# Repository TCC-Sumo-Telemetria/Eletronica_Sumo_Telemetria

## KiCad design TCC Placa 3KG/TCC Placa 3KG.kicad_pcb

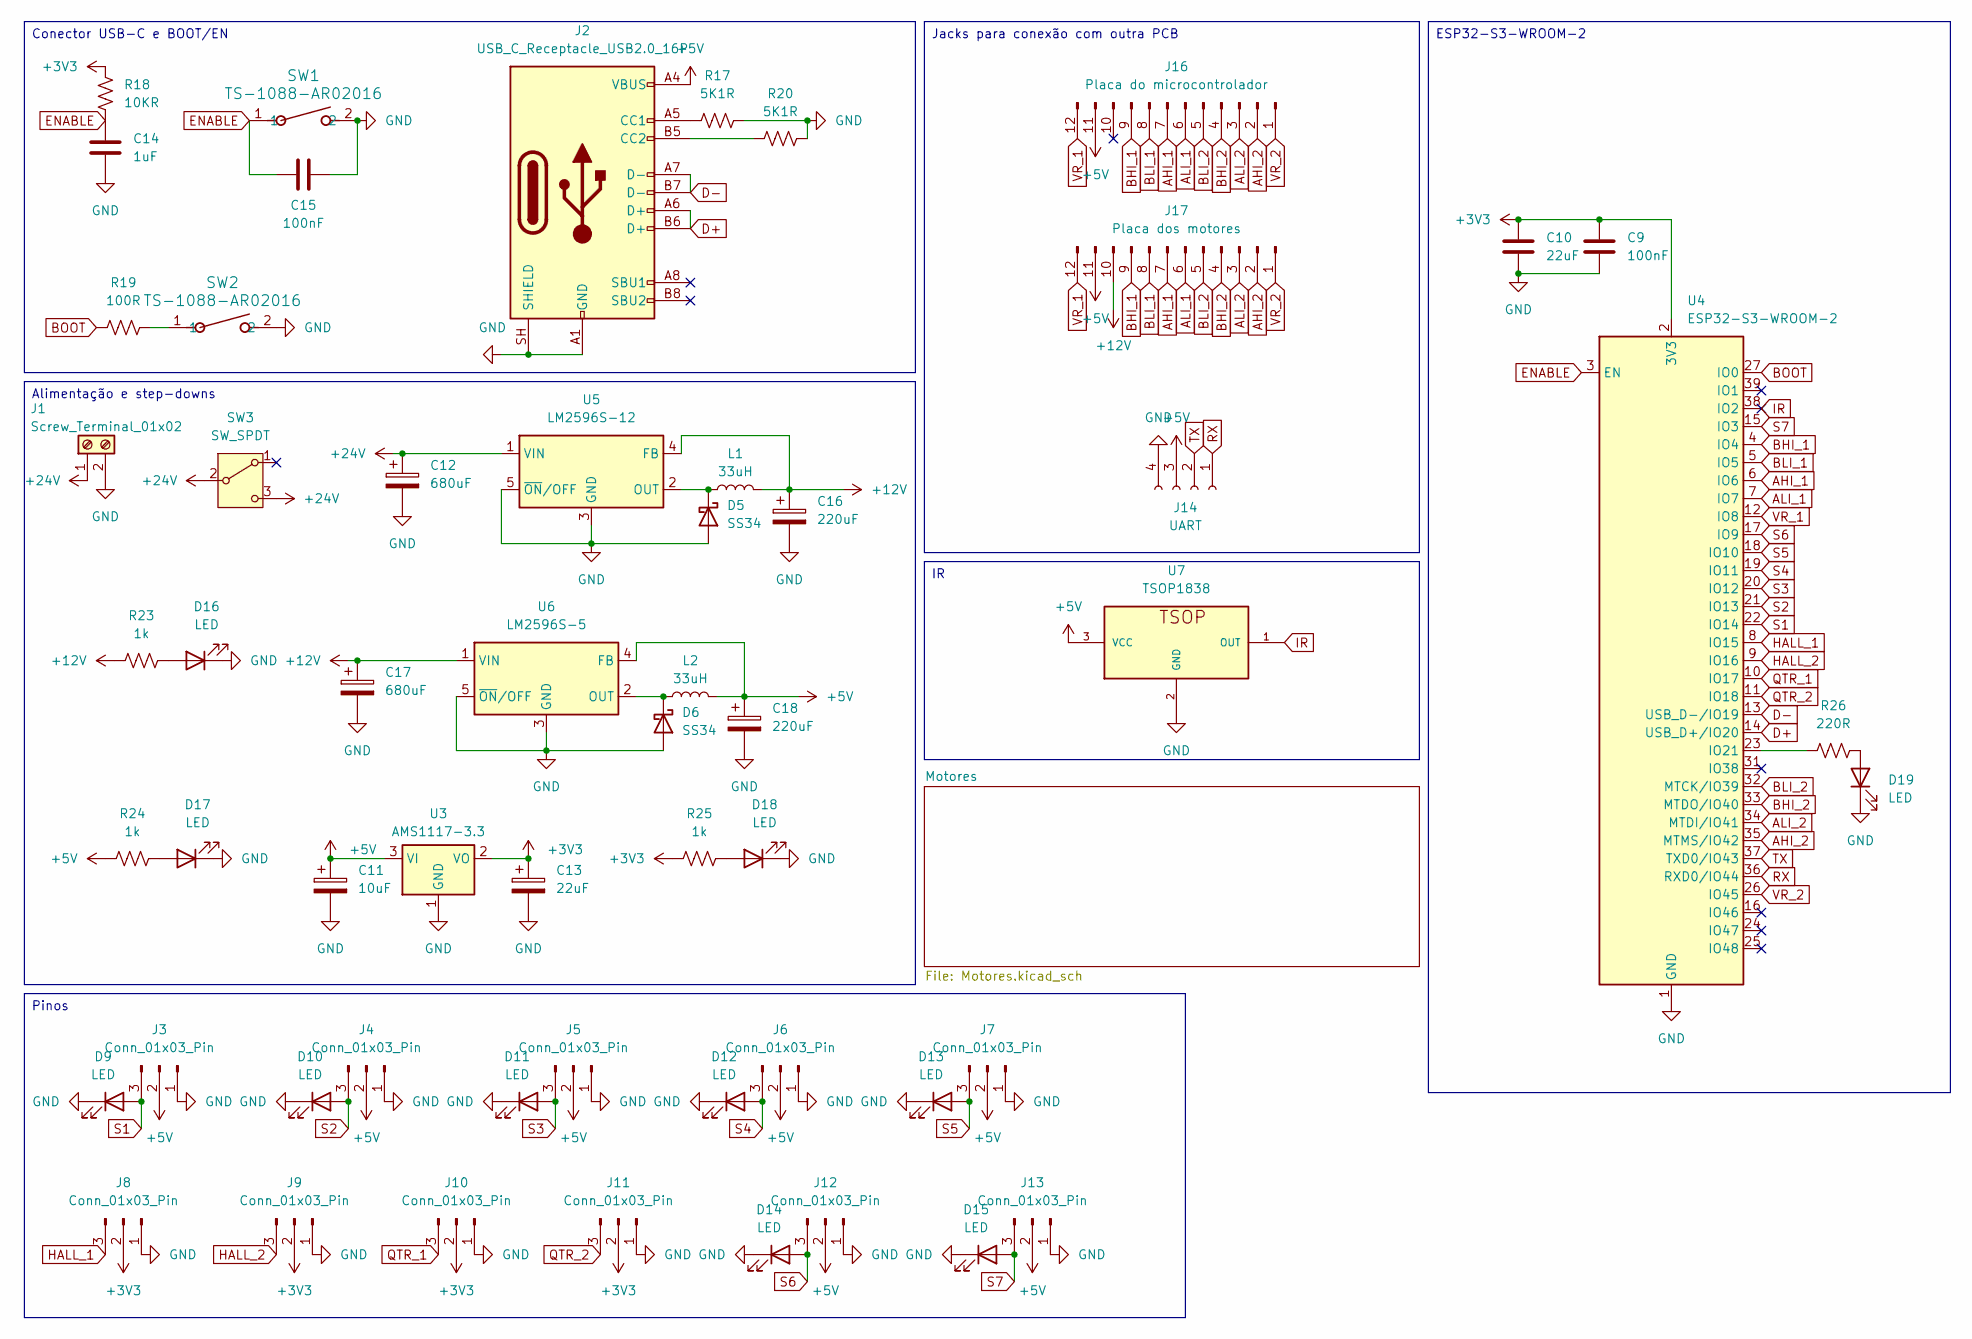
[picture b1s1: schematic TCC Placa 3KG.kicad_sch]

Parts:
C9: 100nF; C_0805_2012Metric
C10: 22uF; C_0805_2012Metric
C11: 10uF; CP_EIA-3528-21_Kemet-B_HandSolder
C12, C17: 680uF; CP_Radial_D10.0mm_P5.00mm
C13: 22uF; CP_EIA-3528-21_Kemet-B_HandSolder
C14: 1uF; C_0805_2012Metric_Pad1.18x1.45mm_HandSolder
C15: 100nF; C_0805_2012Metric_Pad1.18x1.45mm_HandSolder
C16, C18: 220uF; CP_Elec_8x10.5
D5, D6: SS34; D_SMA_Handsoldering
D9, D10, D11, D12, D13, D14, D15, D16, D17, D18, D19: LED; LED_0805_2012Metric_Pad1.15x1.40mm_HandSolder
J1: Screw_Terminal_01x02; TerminalBlock_MaiXu_MX126-5.0-02P_1x02_P5.00mm
J2: USB_C_Receptacle_USB2.0_16P; USB_C_Receptacle_G-Switch_GT-USB-7010ASV
J3, J4, J5, J6, J7, J12, J13: Conn_01x03_Pin; Molex_KK-254_AE-6410-03A_1x03_P2.54mm_Vertical
J8, J9, J10, J11: Conn_01x03_Pin; PinHeader_1x03_P2.54mm_Vertical
J14: UART; PinHeader_1x04_P2.54mm_Vertical
J16: Placa do microcontrolador; PinHeader_1x12_P2.54mm_Vertical
J17: Placa dos motores; PinHeader_1x12_P2.54mm_Vertical
L1, L2: 33uH; L_Bourns-SRU8028_8.0x8.0mm
R17, R20: 5K1R; R_1812_4532Metric_Pad1.30x3.40mm_HandSolder
R18: 10KR; R_0805_2012Metric_Pad1.20x1.40mm_HandSolder
R19: 100R; R_0805_2012Metric_Pad1.20x1.40mm_HandSolder
R23, R24, R25: 1k; R_0603_1608Metric
R26: 220R; R_0603_1608Metric
SW1, SW2: TS-1088-AR02016; SW_TS-1088_XNP
SW3: SW_SPDT; SS-12D10G5_XKB
U3: AMS1117-3.3; SOT-223-3_TabPin2
U4: ESP32-S3-WROOM-2
U5: LM2596S-12; TO-263-5_TabPin3
U6: LM2596S-5; TO-263-5_TabPin3
U7: TSOP1838

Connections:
+3V3: C9.2, C10.2, C13.1, J8.2, J9.2, J10.2, J11.2, R18.1, R25.2, U3.2 (VO), U4.2 (3V3)
+5V: C11.1, C18.1, J2.A4 (VBUS), J2.A9 (VBUS), J2.B4 (VBUS), J2.B9 (VBUS), J3.2, J4.2, J5.2, J6.2, J7.2, J12.2, J13.2, J14.3, J16.11, J17.11, L2.2, R24.2, U3.3 (VI), U6.4 (FB), U7.3 (VCC)
+12V: C16.1, C17.1, J17.10, L1.2, R23.2, U5.4 (FB), U6.1 (VIN); also elsewhere on the board
+24V: C12.1, J1.1, SW3.2 (B), SW3.3 (C), U5.1 (VIN); also elsewhere on the board
AHI_1: J16.7, J17.7, U4.6 (IO6); also elsewhere on the board
AHI_2: J16.2, J17.2, U4.35 (MTMS/IO42); also elsewhere on the board
ALI_1: J16.6, J17.6, U4.7 (IO7); also elsewhere on the board
ALI_2: J16.3, J17.3, U4.34 (MTDI/IO41); also elsewhere on the board
BHI_1: J16.9, J17.9, U4.4 (IO4); also elsewhere on the board
BHI_2: J16.4, J17.4, U4.33 (MTDO/IO40); also elsewhere on the board
BLI_1: J16.8, J17.8, U4.5 (IO5); also elsewhere on the board
BLI_2: J16.5, J17.5, U4.32 (MTCK/IO39); also elsewhere on the board
BOOT: R19.1, U4.27 (IO0)
D+: J2.A6 (D+), J2.B6 (D+), U4.14 (USB_D+/IO20)
D-: J2.A7 (D-), J2.B7 (D-), U4.13 (USB_D-/IO19)
ENABLE: C14.1, C15.1, R18.2, SW1.1, U4.3 (EN)
GND: C9.1, C10.1, C11.2, C12.2, C13.2, C14.2, C15.2, C16.2, C17.2, C18.2, D5.2 (A), D6.2 (A), D9.1 (K), D10.1 (K), D11.1 (K), D12.1 (K), D13.1 (K), D14.1 (K), D15.1 (K), D16.1 (K), D17.1 (K), D18.1 (K), D19.1 (K), J1.2, J2.A1 (GND), J2.A12 (GND), J2.B1 (GND), J2.B12 (GND), J2.SH (SHIELD), J3.1, J4.1, J5.1, J6.1, J7.1, J8.1, J9.1, J10.1, J11.1, J12.1, J13.1, J14.4, R17.2, R20.1, SW1.2, SW2.2, U3.1 (GND), U4.1 (GND), U4.40 (GND), U4.41 (GND), U5.3 (GND), U5.5 (~ON/OFF), U6.3 (GND), U6.5 (~ON/OFF), U7.2 (GND); also elsewhere on the board
HALL_1: J8.3, U4.8 (IO15)
HALL_2: J9.3, U4.9 (IO16)
IR: U4.38 (IO2), U7.1 (OUT)
unnamed: D5.1 (K), L1.1, U5.2 (OUT)
unnamed: D6.1 (K), L2.1, U6.2 (OUT)
unnamed: D16.2 (A), R23.1
unnamed: D17.2 (A), R24.1
unnamed: D18.2 (A), R25.1
unnamed: D19.2 (A), R26.1
unnamed: J2.A5 (CC1), R17.1
unnamed: J2.B5 (CC2), R20.2
unnamed: R19.2, SW2.1
unnamed: R26.2, U4.23 (IO21)
QTR_1: J10.3, U4.10 (IO17)
QTR_2: J11.3, U4.11 (IO18)
RX: J14.1, U4.36 (RXD0/IO44)
S1: D9.2 (A), J3.3, U4.22 (IO14)
S2: D10.2 (A), J4.3, U4.21 (IO13)
S3: D11.2 (A), J5.3, U4.20 (IO12)
S4: D12.2 (A), J6.3, U4.19 (IO11)
S5: D13.2 (A), J7.3, U4.18 (IO10)
S6: D14.2 (A), J12.3, U4.17 (IO9)
S7: D15.2 (A), J13.3, U4.15 (IO3)
TX: J14.2, U4.37 (TXD0/IO43)
VR_1: J16.12, J17.12, U4.12 (IO8); also elsewhere on the board
VR_2: J16.1, J17.1, U4.26 (IO45); also elsewhere on the board

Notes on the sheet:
Pinos
Alimentação e step-downs
ESP32-S3-WROOM-2
Jacks para conexão com outra PCB
Conector USB-C e BOOT/EN

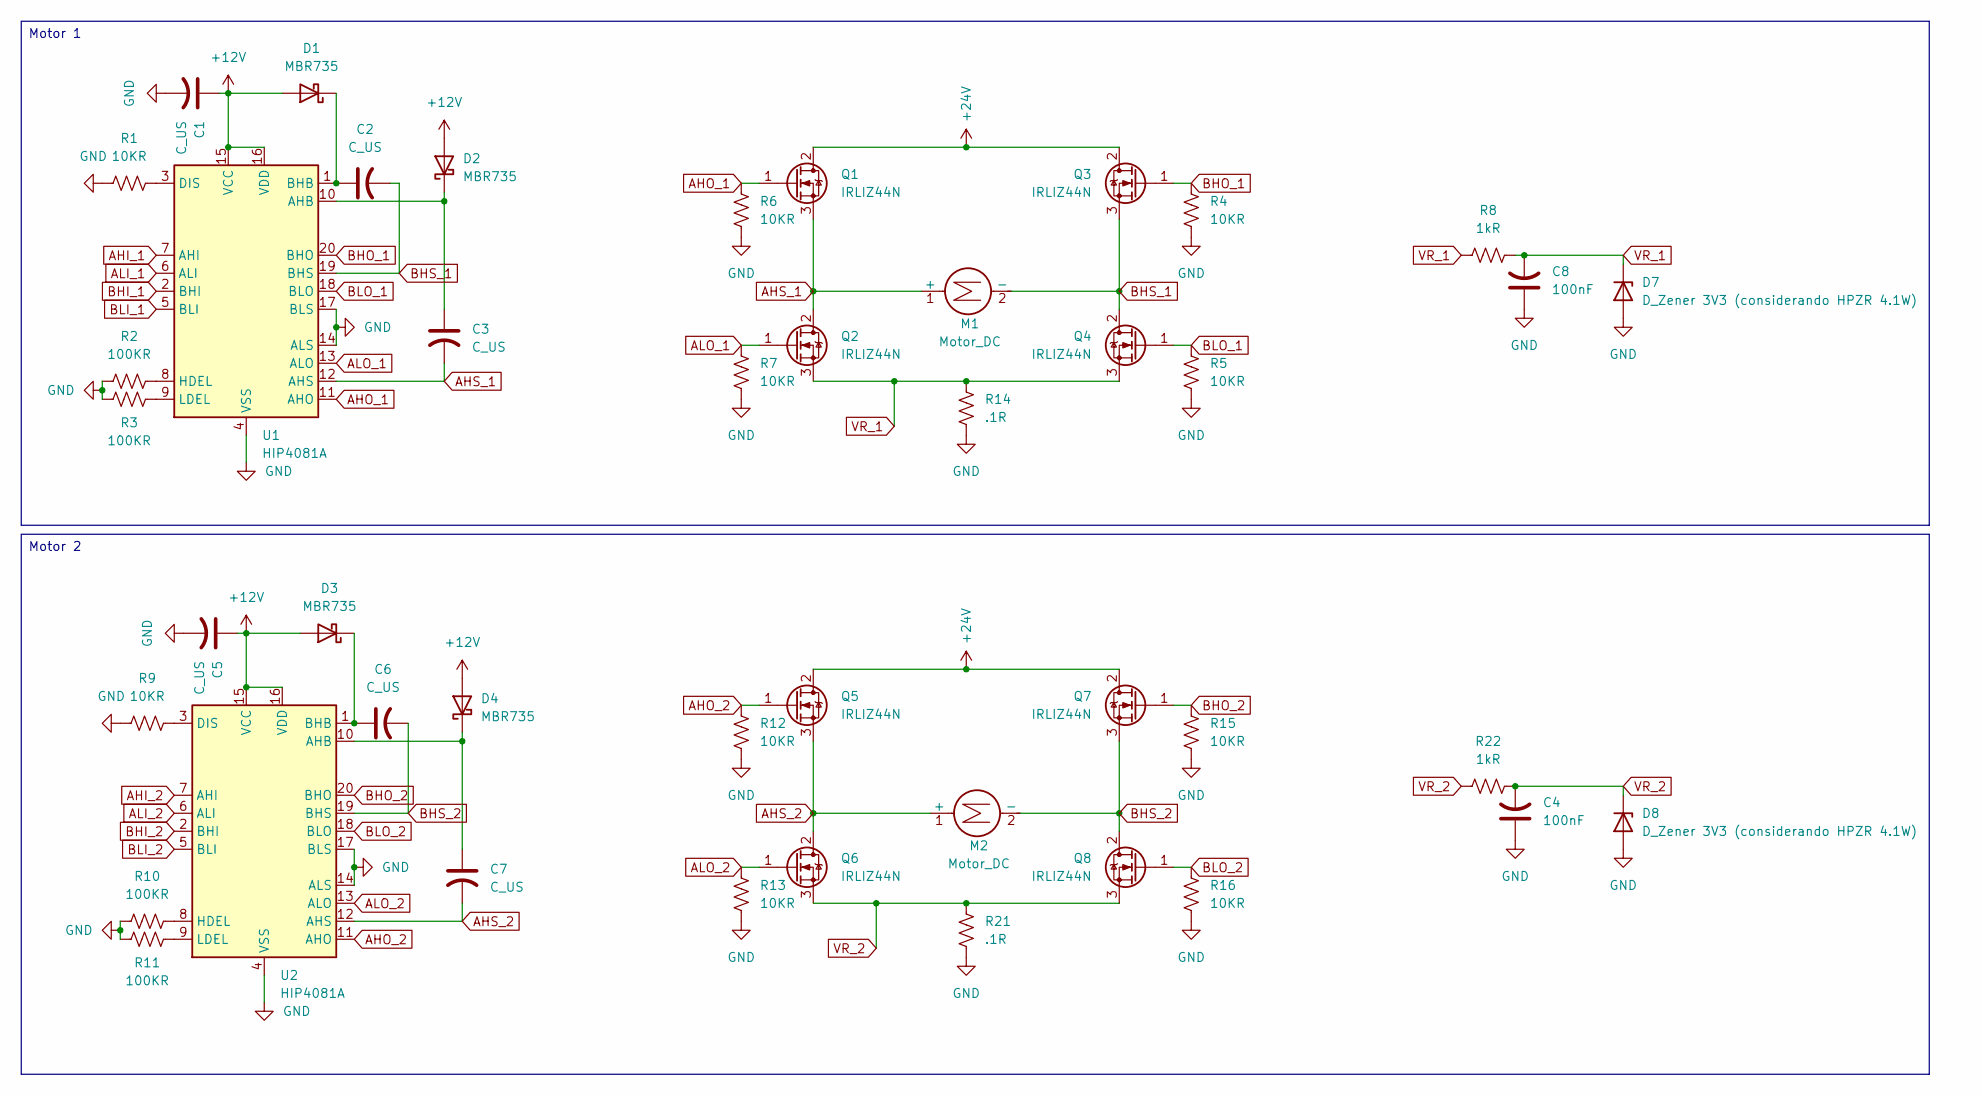
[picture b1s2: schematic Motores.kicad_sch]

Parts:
C1, C2, C3, C5, C6, C7: C_US
C4, C8: 100nF; C_0805_2012Metric
D1, D2, D3, D4: MBR735; TO-220-2_Vertical
D7, D8: D_Zener 3V3 (considerando HPZR 4.1W); D_A-405_P7.62mm_Horizontal
M1, M2: Motor_DC; TerminalBlock_MaiXu_MX126-5.0-02P_1x02_P5.00mm
Q1, Q2, Q3, Q4, Q5, Q6, Q7, Q8: IRLIZ44N; TO-220F-3_Vertical
R1, R9: 10KR
R2, R3, R10, R11: 100KR; R_1206_3216Metric_Pad1.30x1.75mm_HandSolder
R4, R5, R6, R7, R12, R13, R15, R16: 10KR; R_1210_3225Metric_Pad1.30x2.65mm_HandSolder
R8, R22: 1kR; R_0603_1608Metric
R14, R21: .1R; R_0805_2012Metric_Pad1.20x1.40mm_HandSolder
U1, U2: HIP4081A; DIP-20_W7.62mm_LongPads

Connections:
+12V: C1.1, C5.1, D1.2 (A), D2.2 (A), D3.2 (A), D4.2 (A), U1.15 (VCC), U1.16 (VDD), U2.15 (VCC), U2.16 (VDD); also elsewhere on the board
+24V: Q1.2 (D), Q3.2 (D), Q5.2 (D), Q7.2 (D); also elsewhere on the board
AHI_1: U1.7 (AHI); also elsewhere on the board
AHI_2: U2.7 (AHI); also elsewhere on the board
AHO_1: Q1.1 (G), R6.2, U1.11 (AHO)
AHO_2: Q5.1 (G), R12.2, U2.11 (AHO)
AHS_1: C3.2, M1.1 (+), Q1.3 (S), Q2.2 (D), U1.12 (AHS)
AHS_2: C7.2, M2.1 (+), Q5.3 (S), Q6.2 (D), U2.12 (AHS)
ALI_1: U1.6 (ALI); also elsewhere on the board
ALI_2: U2.6 (ALI); also elsewhere on the board
ALO_1: Q2.1 (G), R7.2, U1.13 (ALO)
ALO_2: Q6.1 (G), R13.2, U2.13 (ALO)
BHI_1: U1.2 (BHI); also elsewhere on the board
BHI_2: U2.2 (BHI); also elsewhere on the board
BHO_1: Q3.1 (G), R4.2, U1.20 (BHO)
BHO_2: Q7.1 (G), R15.2, U2.20 (BHO)
BHS_1: C2.2, M1.2 (-), Q3.3 (S), Q4.2 (D), U1.19 (BHS)
BHS_2: C6.2, M2.2 (-), Q7.3 (S), Q8.2 (D), U2.19 (BHS)
BLI_1: U1.5 (BLI); also elsewhere on the board
BLI_2: U2.5 (BLI); also elsewhere on the board
BLO_1: Q4.1 (G), R5.2, U1.18 (BLO)
BLO_2: Q8.1 (G), R16.2, U2.18 (BLO)
GND: C1.2, C4.1, C5.2, C8.1, D7.2 (A), D8.2 (A), R1.1, R2.1, R3.2, R4.1, R5.1, R6.1, R7.1, R9.1, R10.1, R11.2, R12.1, R13.1, R14.1, R15.1, R16.1, R21.1, U1.4 (VSS), U1.14 (ALS), U1.17 (BLS), U2.4 (VSS), U2.14 (ALS), U2.17 (BLS); also elsewhere on the board
unnamed: C2.1, D1.1 (K), U1.1 (BHB)
unnamed: C3.1, D2.1 (K), U1.10 (AHB)
unnamed: C6.1, D3.1 (K), U2.1 (BHB)
unnamed: C7.1, D4.1 (K), U2.10 (AHB)
unnamed: R1.2, U1.3 (DIS)
unnamed: R2.2, U1.8 (HDEL)
unnamed: R3.1, U1.9 (LDEL)
unnamed: R9.2, U2.3 (DIS)
unnamed: R10.2, U2.8 (HDEL)
unnamed: R11.1, U2.9 (LDEL)
VR_1: C8.2, D7.1 (K), Q2.3 (S), Q4.3 (S), R8.1, R8.2, R14.2; also elsewhere on the board
VR_2: C4.2, D8.1 (K), Q6.3 (S), Q8.3 (S), R21.2, R22.1, R22.2; also elsewhere on the board

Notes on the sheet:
Motor 2
Motor 1

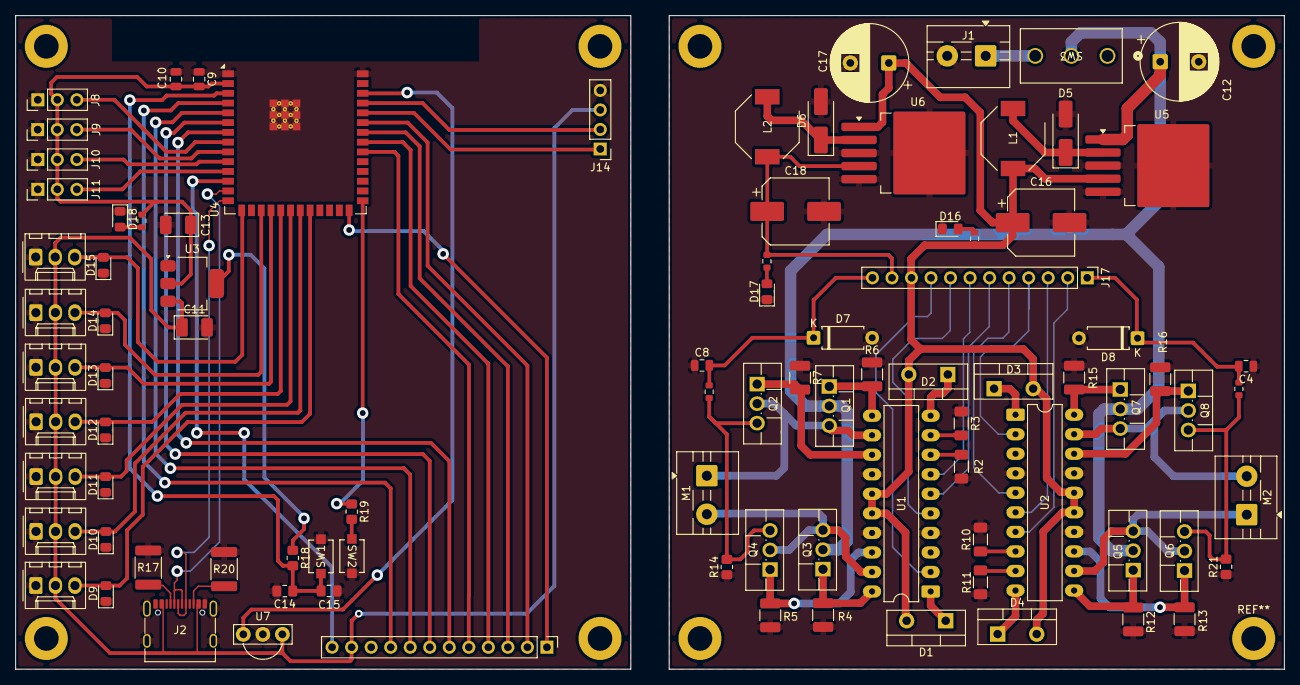
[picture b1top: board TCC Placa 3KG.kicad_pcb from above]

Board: 2 copper layers, 165.0 x 85.0 mm, 91 parts (0 on the bottom side), 61 nets.

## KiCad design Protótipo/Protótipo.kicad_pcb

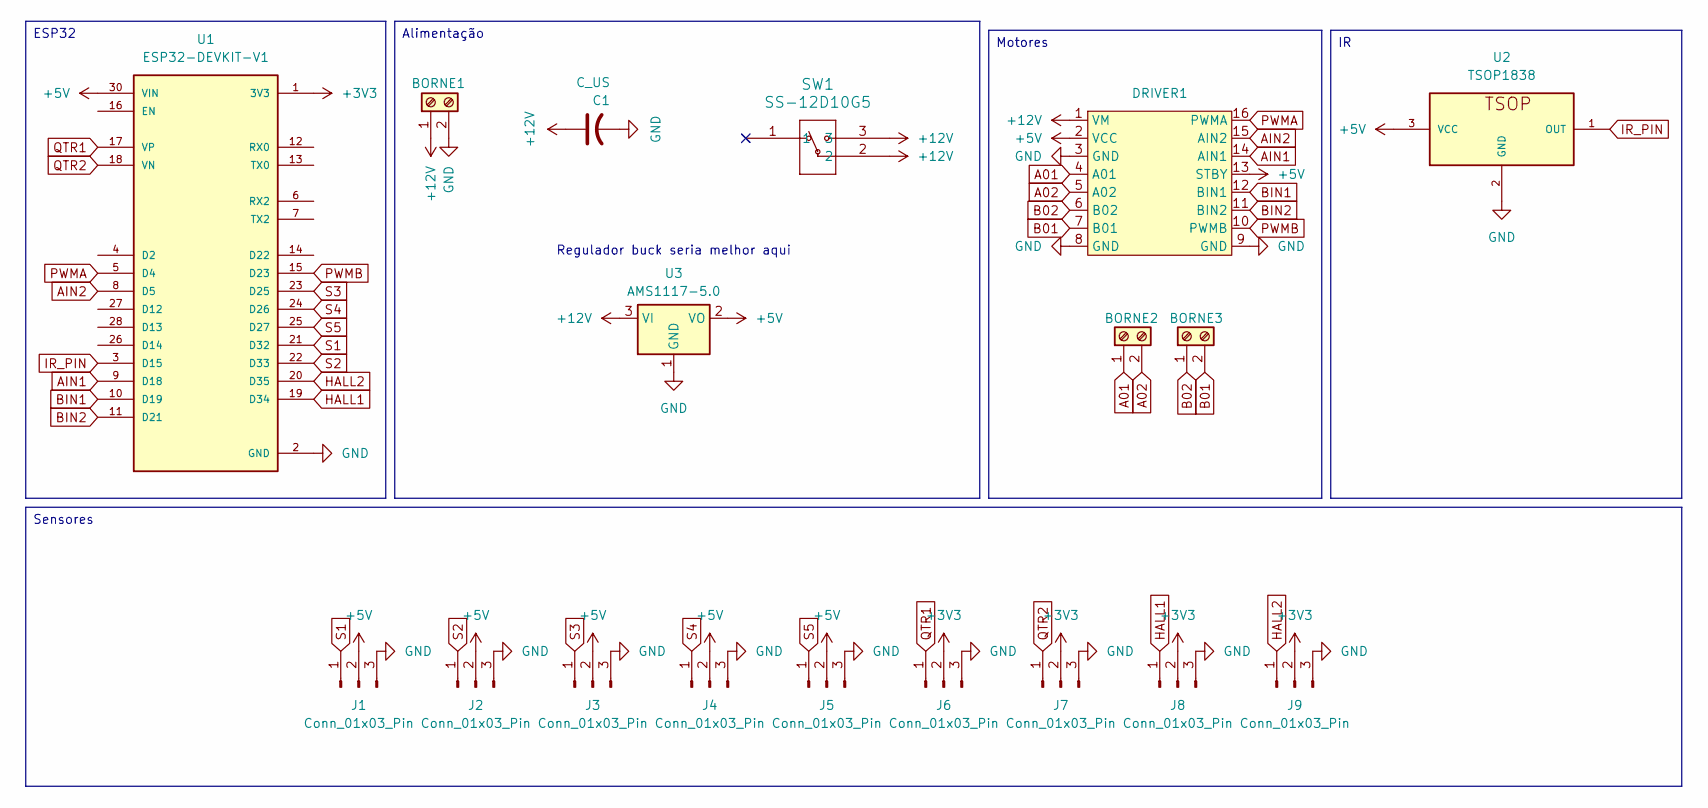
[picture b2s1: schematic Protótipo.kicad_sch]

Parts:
BORNE1, BORNE2, BORNE3: Screw_Terminal_01x02; TerminalBlock_Xinya_XY308-2.54-2P_1x02_P2.54mm_Horizontal
C1: C_US; C_Radial_D4.0mm_H7.0mm_P1.50mm
DRIVER1: Socket_TB6612FNG
J1, J2, J3, J4, J5, J6, J7, J8, J9: Conn_01x03_Pin; Molex_KK-254_AE-6410-03A_1x03_P2.54mm_Vertical
SW1: SS-12D10G5; SS-12D10G5_XKB
U1: ESP32-DEVKIT-V1; MODULE_ESP32_DEVKIT_V1; PARTREV N/A
U2: TSOP1838
U3: AMS1117-5.0; SOT-223-3_TabPin2

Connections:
+3V3: J6.2, J7.2, J8.2, J9.2, U1.1 (3V3)
+5V: DRIVER1.2 (VCC), DRIVER1.13 (STBY), J1.2, J2.2, J3.2, J4.2, J5.2, U1.30 (VIN), U2.3 (VCC), U3.2 (VO)
+12V: BORNE1.1, C1.1, DRIVER1.1 (VM), SW1.2, SW1.3, U3.3 (VI)
A01: BORNE2.1, DRIVER1.4 (A01)
A02: BORNE2.2, DRIVER1.5 (A02)
AIN1: DRIVER1.14 (AIN1), U1.9 (D18)
AIN2: DRIVER1.15 (AIN2), U1.8 (D5)
B01: BORNE3.2, DRIVER1.7 (B01)
B02: BORNE3.1, DRIVER1.6 (B02)
BIN1: DRIVER1.12 (BIN1), U1.10 (D19)
BIN2: DRIVER1.11 (BIN2), U1.11 (D21)
GND: BORNE1.2, C1.2, DRIVER1.3 (GND), DRIVER1.8 (GND), DRIVER1.9 (GND), J1.3, J2.3, J3.3, J4.3, J5.3, J6.3, J7.3, J8.3, J9.3, U1.2 (GND), U1.29 (GND), U2.2 (GND), U3.1 (GND)
HALL1: J8.1, U1.19 (D34)
HALL2: J9.1, U1.20 (D35)
IR_PIN: U1.3 (D15), U2.1 (OUT)
PWMA: DRIVER1.16 (PWMA), U1.5 (D4)
PWMB: DRIVER1.10 (PWMB), U1.15 (D23)
QTR1: J6.1, U1.17 (VP)
QTR2: J7.1, U1.18 (VN)
S1: J1.1, U1.21 (D32)
S2: J2.1, U1.22 (D33)
S3: J3.1, U1.23 (D25)
S4: J4.1, U1.24 (D26)
S5: J5.1, U1.25 (D27)

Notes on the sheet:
Regulador buck seria melhor aqui
Sensores
ESP32
Motores
Alimentação

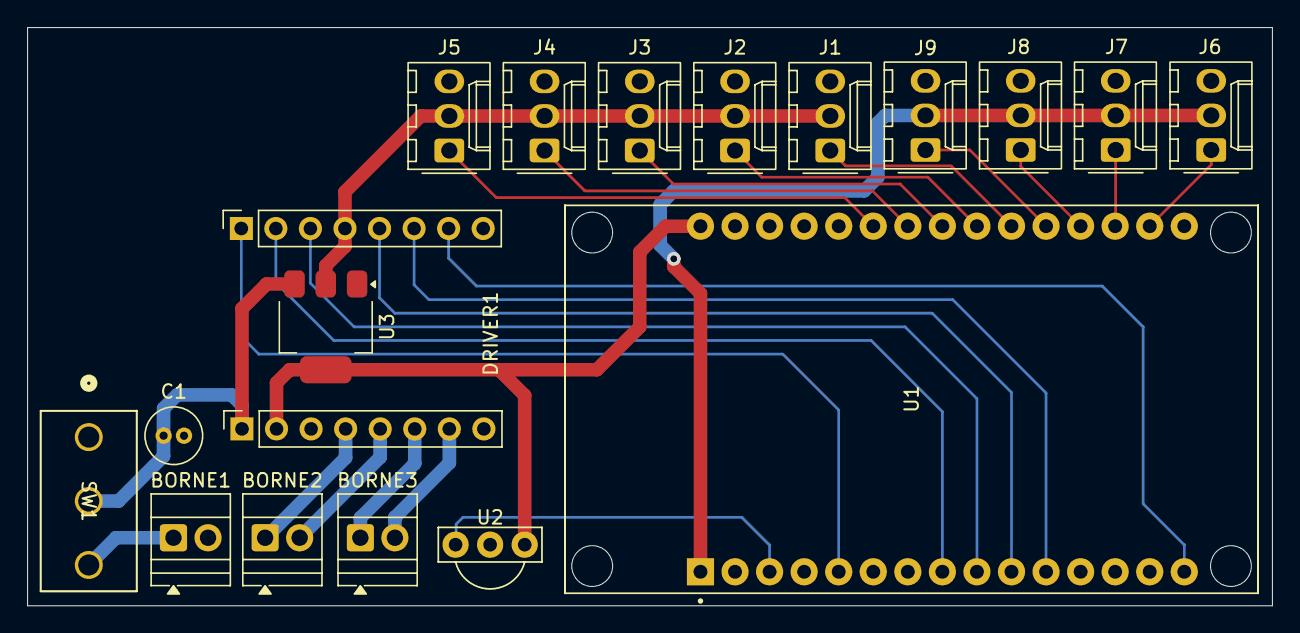
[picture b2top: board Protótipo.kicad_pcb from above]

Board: 2 copper layers, 91.5 x 42.5 mm, 18 parts (0 on the bottom side), 24 nets.

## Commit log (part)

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2026-05-04 🎉 Commit inicial: Protótipo com componentes de mini sumô
